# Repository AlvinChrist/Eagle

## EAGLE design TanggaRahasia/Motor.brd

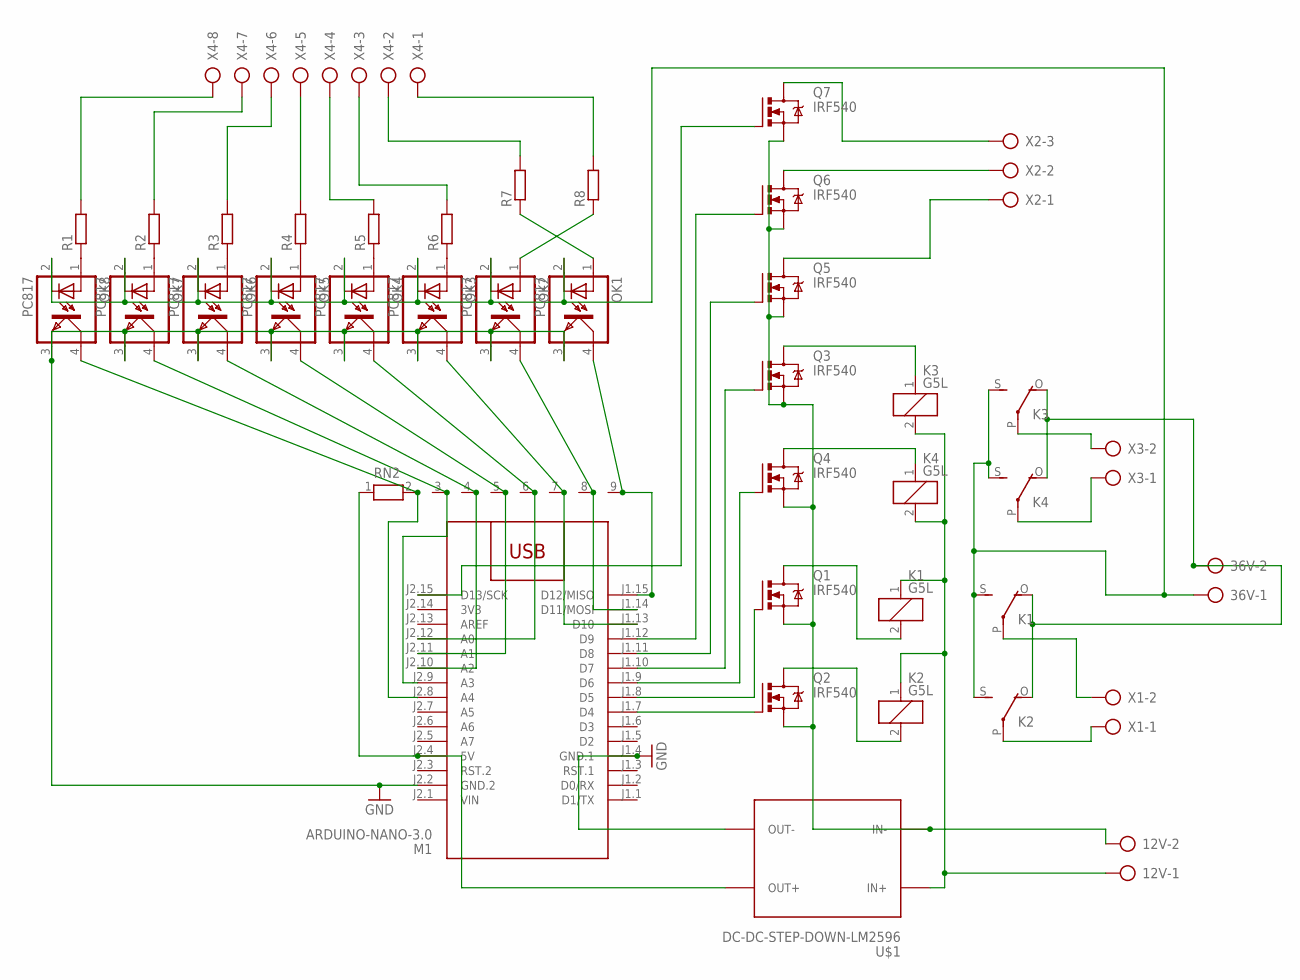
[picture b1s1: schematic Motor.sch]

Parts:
12V, 36V: AK300/2
K1, K2, K3, K4: G5L; G5LE
M1: ARDUINO-NANO-3.0
OK1, OK2, OK3, OK4, OK5, OK6, OK7, OK8: PC817; DIL04
Q1, Q2, Q3, Q4, Q5, Q6, Q7: IRF540; TO220BV
R1, R2, R3, R4, R5, R6, R7, R8: R-EU_0204/7; 0204/7
RN2: RN08; RN-9
U$1: DC-DC-STEP-DOWN-LM2596
X1, X3: AK300/2
X2: AK300/3
X4: AK300/8

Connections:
3V3: M1.J2.14 (3V3)
+36V: 36V.2, K1.O, K2.O, K3.O, K4.O
-36V: 36V.1, K1.S, K2.S, K3.S, K4.S, OK1.2 (C), OK2.2 (C), OK3.2 (C), OK4.2 (C), OK5.2 (C), OK6.2 (C), OK7.2 (C), OK8.2 (C)
GND: M1.J1.4 (GND.1), M1.J2.2 (GND.2), OK1.3 (EMIT), OK2.3 (EMIT), OK3.3 (EMIT), OK4.3 (EMIT), OK5.3 (EMIT), OK6.3 (EMIT), OK7.3 (EMIT), OK8.3 (EMIT), U$1.OUT-
GND12: 12V.2, Q1.S, Q2.S, Q3.S, Q4.S, Q5.S, Q6.S, Q7.S, U$1.IN-
unnamed: Q7.D, X2.3
unnamed: M1.J1.15 (D12/MISO), OK1.4 (COL), RN2.9
unnamed: K2.2, Q2.D
unnamed: K1.2, Q1.D
unnamed: M1.J2.15 (D13/SCK), Q7.G
unnamed: M1.J2.4 (5V), RN2.1, U$1.OUT+
unnamed: M1.J1.7 (D4), Q2.G
unnamed: 12V.1, K1.1, K2.1, K3.2, K4.2, U$1.IN+
unnamed: M1.J1.8 (D5), Q1.G
unnamed: K2.P, X1.1
unnamed: K1.P, X1.2
unnamed: Q5.D, X2.1
unnamed: OK2.1 (A), R8.1
unnamed: K3.P, X3.2
unnamed: K4.P, X3.1
unnamed: Q6.D, X2.2
unnamed: K3.1, Q3.D
unnamed: K4.1, Q4.D
unnamed: M1.J1.9 (D6), Q4.G
unnamed: M1.J1.10 (D7), Q3.G
unnamed: M1.J2.8 (A4), OK8.4 (COL), RN2.2
unnamed: OK1.1 (A), R7.1
unnamed: M1.J1.11 (D8), Q5.G
unnamed: M1.J1.12 (D9), Q6.G
unnamed: M1.J2.10 (A2), OK6.4 (COL), RN2.4
unnamed: M1.J2.11 (A1), OK5.4 (COL), RN2.5
unnamed: M1.J2.12 (A0), OK4.4 (COL), RN2.6
unnamed: M1.J2.9 (A3), OK7.4 (COL), RN2.3
unnamed: OK8.1 (A), R1.1
unnamed: OK7.1 (A), R2.1
unnamed: OK6.1 (A), R3.1
unnamed: OK5.1 (A), R4.1
unnamed: OK4.1 (A), R5.1
unnamed: OK3.1 (A), R6.1
unnamed: R1.2, X4.8
unnamed: R2.2, X4.7
unnamed: R3.2, X4.6
unnamed: R4.2, X4.5
unnamed: R5.2, X4.4
unnamed: R6.2, X4.3
unnamed: R7.2, X4.2
unnamed: R8.2, X4.1
unnamed: M1.J1.13 (D10), OK3.4 (COL), RN2.7
unnamed: M1.J1.14 (D11/MOSI), OK2.4 (COL), RN2.8
VIN: M1.J2.1 (VIN)

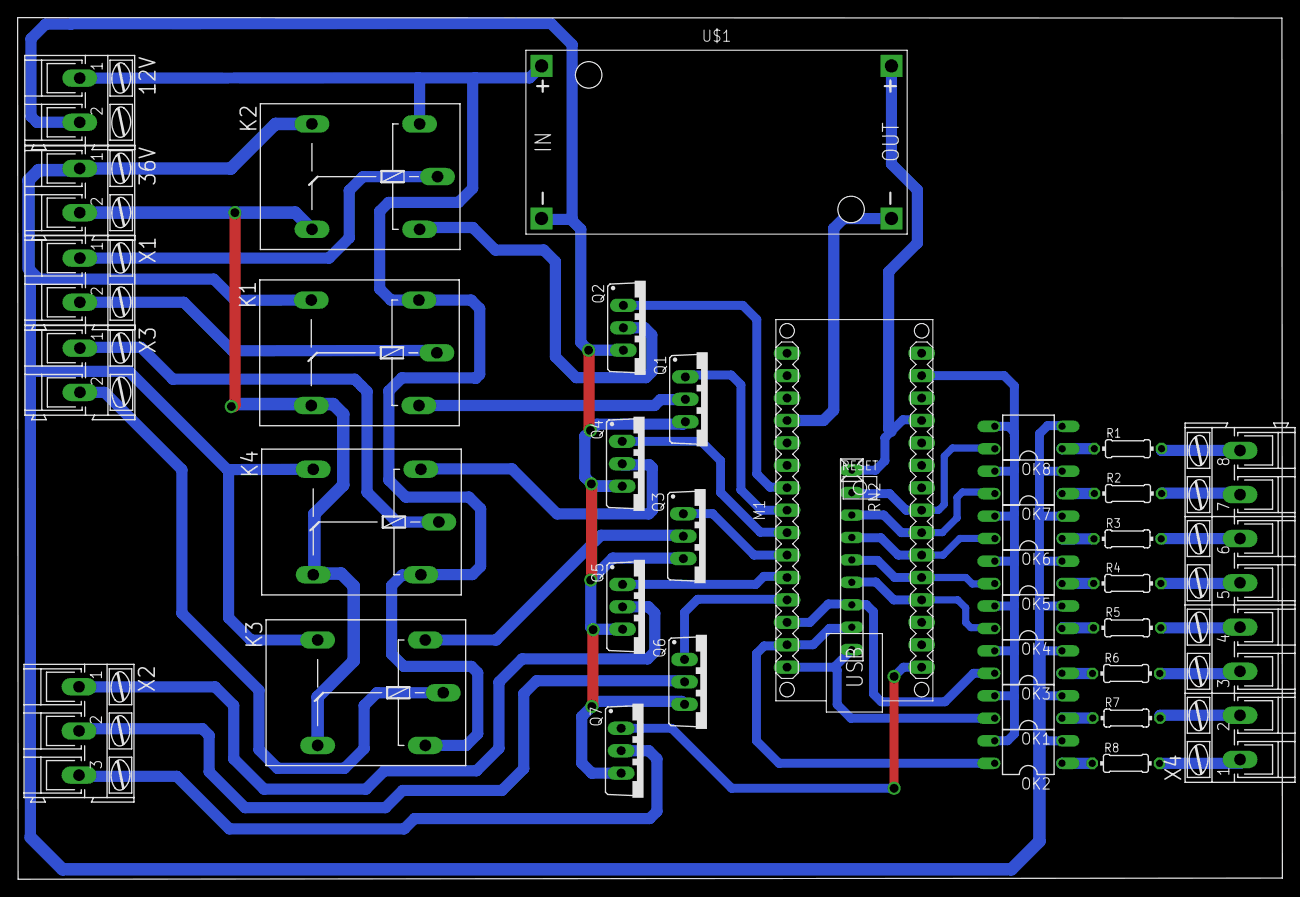
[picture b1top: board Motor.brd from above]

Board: 2 copper layers, 143.2 x 97.6 mm, 36 parts (0 on the bottom side), 48 nets.

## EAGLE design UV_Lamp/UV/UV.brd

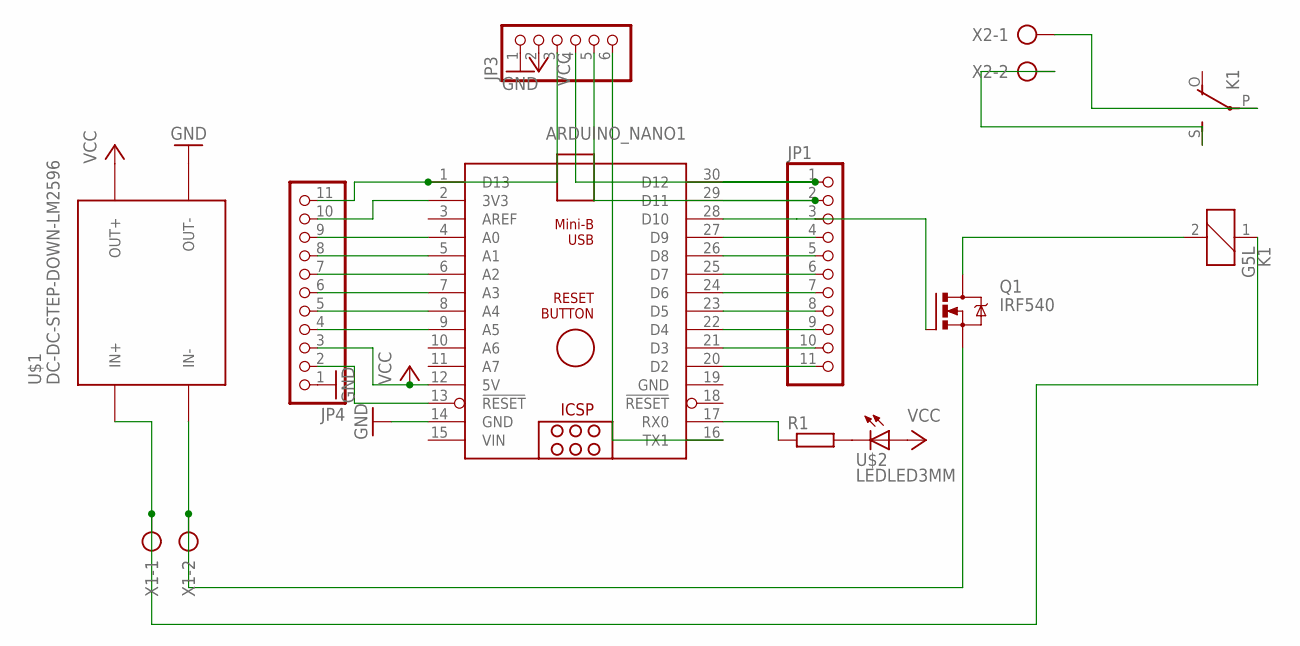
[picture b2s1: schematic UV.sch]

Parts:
ARDUINO_NANO1: ARDUINO_NANO
JP1, JP4: PINHD-1X11; 1X11
JP3: PINHD-1X6; 1X06
K1: G5L; G5LE
Q1: IRF540; TO220BV
R1: R-EU_0204/7; 0204/7
U$1: DC-DC-STEP-DOWN-LM2596
U$2: LEDLED3MM; LED3MM
X1, X2: AK300/2

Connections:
GND: ARDUINO_NANO1.14 (GND), ARDUINO_NANO1.19 (GND), JP3.1, JP4.1, U$1.OUT-
unnamed: K1.1, U$1.IN+, X1.1
unnamed: ARDUINO_NANO1.1 (D13), JP3.3, JP4.11
unnamed: ARDUINO_NANO1.30 (D12), JP1.1, JP3.4
unnamed: K1.2, Q1.D
unnamed: ARDUINO_NANO1.29 (D11), JP1.2, JP3.5
unnamed: ARDUINO_NANO1.16 (TX1), JP3.6
unnamed: K1.P, X2.1
unnamed: R1.2, U$2.K (C)
unnamed: ARDUINO_NANO1.17 (RX0), R1.1
unnamed: ARDUINO_NANO1.27 (D9), JP1.4
unnamed: ARDUINO_NANO1.26 (D8), JP1.5
unnamed: ARDUINO_NANO1.25 (D7), JP1.6
unnamed: K1.S, X2.2
unnamed: ARDUINO_NANO1.24 (D6), JP1.7
unnamed: ARDUINO_NANO1.23 (D5), JP1.8
unnamed: ARDUINO_NANO1.22 (D4), JP1.9
unnamed: ARDUINO_NANO1.21 (D3), JP1.10
unnamed: ARDUINO_NANO1.20 (D2), JP1.11
unnamed: Q1.S, U$1.IN-, X1.2
unnamed: ARDUINO_NANO1.2 (3V3), JP4.10
unnamed: ARDUINO_NANO1.4 (A0), JP4.9
unnamed: ARDUINO_NANO1.5 (A1), JP4.8
unnamed: ARDUINO_NANO1.6 (A2), JP4.7
unnamed: ARDUINO_NANO1.7 (A3), JP4.6
unnamed: ARDUINO_NANO1.8 (A4), JP4.5
unnamed: ARDUINO_NANO1.9 (A5), JP4.4
unnamed: ARDUINO_NANO1.13 (!RESET), JP4.2
unnamed: ARDUINO_NANO1.28 (D10), JP1.3, Q1.G
VCC: ARDUINO_NANO1.12 (5V), JP3.2, JP4.3, U$1.OUT+, U$2.A
VIN: ARDUINO_NANO1.15 (VIN)

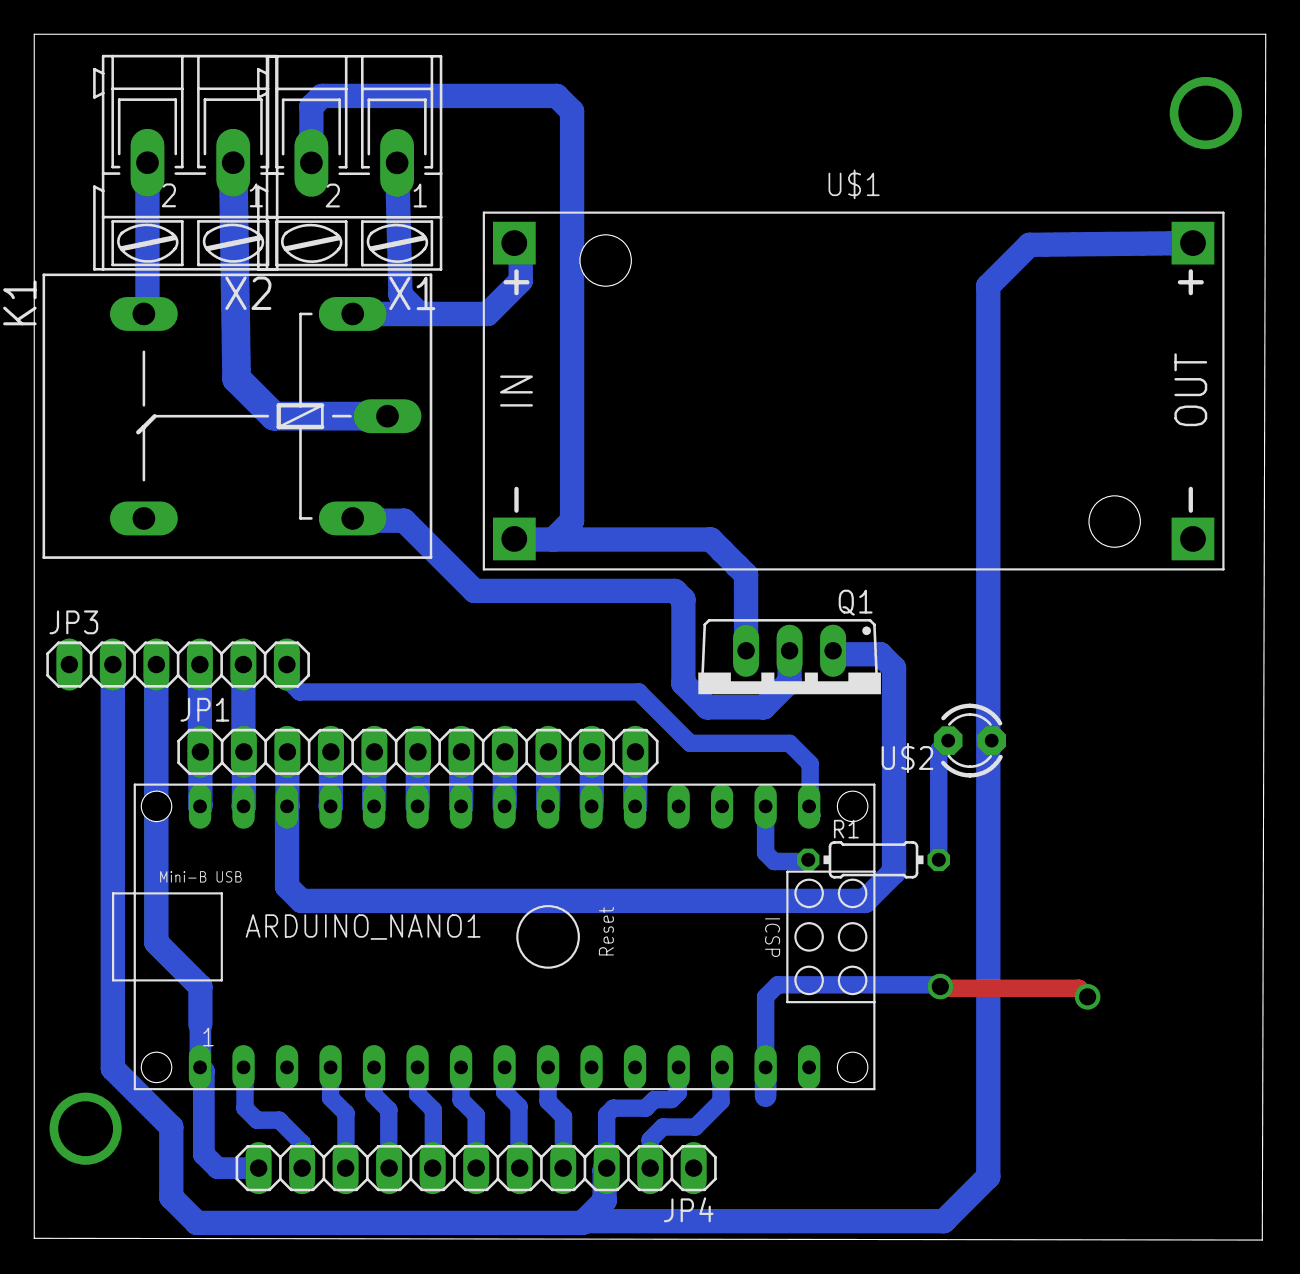
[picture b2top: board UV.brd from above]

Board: 2 copper layers, 71.9 x 70.4 mm, 11 parts (0 on the bottom side), 30 nets.

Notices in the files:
parts and their libraries:
diy-modules: Released under the Creative Commons Attribution 4.0 International License: http://creativecommons.org/licenses/by/4.0
